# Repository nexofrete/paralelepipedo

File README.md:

# paralelepipedo

- [`tda7294/`](tda7294/README.md): amplificador de potência com TDA7294, com esquema, placa de face simples (PDF para transferência térmica e Gerber) e lista de material.

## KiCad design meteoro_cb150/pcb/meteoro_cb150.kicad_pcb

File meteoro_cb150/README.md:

# Meteoro Amplifier — Pré Power CB150

Montagem do esquema **Pré Power CB150** (Poi 20.60.40.012, rev. 0.0, 18/06/2007):
pré-amplificador com op-amps TL082/TL071, equalização passiva e amplificador
de potência classe AB discreto (±55 V, par 2SC5200/2SA1943).

Esta versão inclui **melhorias** sobre o esquema original (proteções, espelho
de corrente etc.); veja [Melhorias aplicadas](#melhorias-aplicadas). Os
componentes novos ou alterados estão marcados com ★ nas listas.

| Arquivo | Conteúdo |
|---|---|
| `esquema_eletrico.pdf` | **Esquema elétrico** da versão com melhorias (3 folhas: pré, potência, fonte); também em PNG (`esquema_*.png`) |
| `meteoro_cb150.cir` | Netlist SPICE completa (pré + potência), com modelos, pronta para o ngspice |
| `fonte.cir` | Fonte de alimentação (trafo, ponte KBPC606, filtros, reguladores ±12 V) |
| `pcb/meteoro_cb150_pcb.pdf` | **Placa de circuito impresso em PDF** (dupla face: as duas faces em 1:1 para transferência, montagem) |
| `pcb/meteoro_cb150_gerber.zip` | Gerber (RS-274X) + furação Excellon — para Proteus, fabricantes e qualquer CAM |
| `pcb/fabricacao/` | Os mesmos Gerbers soltos, DXF de cada face e posição dos componentes (CSV) |
| `pcb/relacao_componentes.csv` | Relação de componentes da placa (lista de compras), abre no Excel/LibreOffice |
| `pcb/meteoro_cb150.kicad_pcb` | A mesma placa em KiCad (abre no KiCad 7+, permite gerar Gerber) |

```sh
ngspice -b meteoro_cb150.cir   # ponto de operação, resposta AC e transiente 1 kHz
ngspice -b fonte.cir           # tensões da fonte
esquema/gerar.sh               # redesenha o esquema elétrico (precisa de schemdraw e matplotlib)
```

## Melhorias aplicadas

| Melhoria | Componentes | Para quê |
|---|---|---|
| Espelho de corrente no par diferencial | QM1, QM2 (MPSA42), RM1, RM2 (100 Ω) | menos distorção, offset ≈ 0 |
| Degeneração de emissor + cauda com 5,2 mA | R37, R38 (47 Ω), R15 3k3 → 1k6 | dobra o slew rate e mantém a estabilidade |
| Resistor de emissor e limitador no VAS | R19 560 Ω → 33 Ω no emissor de Q3, Q9 (BC546) | limita o VAS a ~18 mA (necessário para o limitador de saída funcionar) |
| Proteção contra curto na saída | QL1 (BC546), QL2 (BC556), R32/R34 (3k3), R33/R35 (1k) | limita a corrente de saída a ~8,5 A de pico |
| Resistor entre os drivers | R31 (220 Ω) entre emissores de Q5 e Q4 | desligamento mais rápido dos transistores de saída |
| Bobina de saída | L1: 1 µH (≈ 12 voltas de fio 1 mm) enrolada sobre resistor de 10 Ω/2 W | estabilidade com cabos longos e carga capacitiva |
| Offset equilibrado | R17 3k3 → 27k, R16 120 Ω → 1k | mesma impedância nas bases de Q1 e Q2 (ganho continua 28×) |
| Fusíveis nos trilhos | F1, F2 (5 A rápido, porta-fusível 5×20 de placa) | protege alto-falante e transistores se algo entrar em curto |
| Filtro maior | C19, C20 4700 µF → **10 000 µF**/63 V | menos ripple e queda de tensão em potência alta |

Não incluída na placa: **proteção contra DC no alto-falante com relé**. É
recomendada (módulo pronto de proteção para alto-falante, ligado entre SPEAKER
e a caixa).

## Resultado da simulação (carga 8 Ω, bias ≈ 35 mA)

Comparação do estágio de potência original com o melhorado (modelos de
transistor aproximados — valem como comparação):

| Grandeza | Original | Melhorado |
|---|---|---|
| Offset DC na saída | +120 mV | **+4 mV** |
| Distorção 1 kHz / 50 W | 0,21 % | **0,06 %** |
| Distorção 10 kHz / 50 W | 1,7 % | **0,24 %** |
| Distorção 20 kHz / 140 W | 11,6 % | **0,57 %** |
| Overshoot em degrau, 8 Ω ‖ 2,2 µF | 0,1 % | 0,4 % (estável) |
| Corrente de pico com saída em curto (0,1 Ω) | +21 A / −55 A (queima) | **±8,5 A** (limitada) |

| Grandeza | Valor |
|---|---|
| +12 V / −12 V (zener 1N4742A) | +12,1 V / −12,1 V |
| Trilhos com secundário 2 × 39 VAC | ±54 V |
| Referência da fonte de corrente (D3) | 9,1 V |
| Corrente de cauda do par Q1/Q2 | ≈ 5,2 mA |
| Corrente do VAS (Q3) | ≈ 10 mA |
| Ganho do power (R17/R16) | 1 + 27k/1k = 28× (29 dB) |

## Lista de materiais

### Resistores (1/4 W, 5% salvo indicação)
| Ref. | Valor | | Ref. | Valor |
|---|---|---|---|---|
| R1 | 1k5 | | R16 ★ | 1k |
| R2 | 220k | | R17 ★ | 27k |
| R3 | 2k7 | | R19 ★ | 33 Ω |
| R4 | 22k | | R20 | 2k2 **2 W** |
| R5 | 2k7 | | R21 | 1k5 |
| R6 | 12k | | R22 | 680 Ω |
| R7 | 270k | | R23, R24 | 2k7 (½ W) |
| R8 | 22k | | R26 | 4,7 Ω **2 W** |
| R9 | 2k2 | | R27, R28 | 0,33 Ω **5 W** |
| R10 | 47k | | R29 | 12k |
| R12 | 4k7 | | R30 | 470 Ω |
| R13 | 10k | | R50 | 47k |
| R14 | 4k7 | | R88 | 2k2 **2 W** |
| R15 ★ | 1k6 | | R100 | 5k6 (½ W) |
| R101 | 1k | | R102 | 27k |
| R31 ★ | 220 Ω | | R32, R34 ★ | 3k3 |
| R33, R35 ★ | 1k | | R37, R38 ★ | 47 Ω |
| RM1, RM2 ★ | 100 Ω | | L1 ★ | 10 Ω **2 W** com 1 µH enrolado (ver melhorias) |

### Potenciômetros
| Ref. | Valor | Função |
|---|---|---|
| RV1 | 20k linear (B) | ganho/master do CI2 (ligado como reostato) |
| RV2 | 100k linear (B) | agudos |
| RV3 | 10k linear (B) | equalização (reostato, cursor ligado a um extremo) |
| RV4 | 50k log (A) | equalização (reostato) |
| RV5 | 1k trimpot multivoltas | **ajuste de corrente de repouso (bias)** |

### Capacitores
| Ref. | Valor | Tipo |
|---|---|---|
| C1 | 22 nF | poliéster |
| C2 | 10 µF/63 V | eletrolítico |
| C3, C13 | 330 pF | cerâmico |
| C4, C10 | 2,2 nF | poliéster |
| C5 | 100 nF | poliéster |
| C6 | 47 nF | poliéster |
| C7 | 120 pF | cerâmico |
| C8 | 22 µF/63 V | eletrolítico |
| C9 | 1 µF | poliéster |
| C11 | 22 nF | poliéster |
| C12 | 220 µF/63 V | eletrolítico |
| C14 | 470 pF | cerâmico 100 V |
| C15 | 47 µF/63 V | eletrolítico (no esquema 50 V; use 63 V) |
| C16 | 10 µF/63 V | eletrolítico |
| C17 | 100 nF/250 V | poliéster |
| C18 | 10 µF/63 V | eletrolítico |
| C19, C20 ★ | 10 000 µF/63 V | eletrolítico snap-in (35 mm) |
| C21 | 1 µF | poliéster |
| C100 | 2,2 µF/63 V | eletrolítico |
| C101 | 4,7 µF/50 V | eletrolítico |

> No esquema "22K", "47K", "100K", "2K2" em capacitores significam **nF**
> (22K = 22 nF, 100K = 100 nF, 2K2 = 2,2 nF).

### Semicondutores
| Ref. | Peça | Observação |
|---|---|---|
| CI1 | TL082 | duplo (CI1A + CI1B) |
| CI2 | TL071 | pinos 1/5 (BAL) sem ligação |
| Q1, Q2 | MPSA92 (PNP 300 V) | parear hFE |
| Q3, Q5 | BD139 | Q5 em dissipador pequeno |
| Q4 | BD140 | em dissipador pequeno |
| Q6 | 2SA1943 | dissipador principal, isolado (mica/silicone) |
| Q7 | 2SC5200 | dissipador principal, isolado |
| Q8 | MPSA42 | **colar no dissipador** dos transistores de saída (compensação térmica) |
| QM1, QM2 ★ | MPSA42 | espelho de corrente (de preferência com hFE parecido) |
| Q9, QL1 ★ | BC546 | limitadores (VAS e saída positiva) |
| QL2 ★ | BC556 | limitador (saída negativa) |
| D1, D2 | 1N4742A | zener 12 V 1 W |
| D3 | 1N4739 | zener 9,1 V (a nota do esquema cita "D100 – 1N4742", ver observações) |
| PT1 | KBPC606 | ponte retificadora 6 A, no chassi |

### Outros
- TR: transformador 127/220 V → **2 × 39 VAC** com center tap, ≥ 250 VA, fusível no primário.
- J1: jaque P10 mono; CH1: chave 1 polo (ganho); bornes SPEAKER e LINE OUT.
- Dissipador ≥ 0,5 °C/W para Q6/Q7, isoladores, pasta térmica.
- ★ F1, F2: fusíveis 5×20 mm de 5 A rápidos + porta-fusíveis de placa.

## Placa de circuito impresso (`pcb/`)

Placa **dupla face** de 230 × 145 mm, **sem jumpers** (só 4 vias), com 98
itens: os componentes do esquema com as melhorias, conectores para as peças
de painel, 2 capacitores de desacoplamento de 100 nF nos op-amps (CD1/CD2) e
a ponte de terra JGND. As melhorias acrescentam ligações que cruzam o estágio
de saída; em face simples isso exigiria cerca de 30 jumpers, por isso a placa
passou a ser dupla face.

- **Relação de componentes** (páginas 2–4 do PDF e `relacao_componentes.csv`):
  tirada da própria placa, agrupada por valor, com as peças de painel à parte.
- **Cobre do lado da solda** (B.Cu), em escala 1:1.
- **Cobre do lado dos componentes** (F.Cu), já espelhado para a
  transferência. Alinhe as duas faces pelos 4 furos de fixação.
- **Montagem**: lado dos componentes (referência e valor de cada peça).
- **Sobreposição**: as duas faces juntas.
- Imprima a 100% (sem "ajustar à página"); o contorno deve medir exatamente
  230 × 145 mm.
- Em placa caseira (sem furos metalizados): passe um fio nas 4 vias e solde
  dos dois lados, e solde **também por cima** os pads que têm trilha na face
  de cima. Ou mande fabricar: o `.kicad_pcb` gera Gerber no KiCad 7+.
- O GND de sinal tem plano de cobre nas duas faces. O GND de potência
  (capacitores de filtro, Zobel, alto-falante) só se une a ele pela ponte
  **JGND** — aterramento em estrela.
- Q4/Q5/Q6/Q7 ficam na borda superior para um único dissipador; Q8 deve ficar
  encostado nele (com fios, se preciso) para o bias acompanhar a temperatura.
- Trilhas: 0,75 mm (sinal), 1,2 mm (GND, bases), 2,0 mm (±55 V, saída,
  emissores); isolação mínima de 0,5 mm, verificada com o DRC do KiCad
  (`verificar.py`).

### Abrir no Proteus

O formato de projeto do Proteus (`.pdsprj`) é fechado, então não há como
gerá-lo diretamente. Use os arquivos de fabricação:

- **Gerber**: no Proteus 8, *File → Import → Gerber* (ou o *Gerber Viewer*),
  apontando para os arquivos de `meteoro_cb150_gerber.zip`
  (`.gtl` = cobre de cima, `.gbl` = cobre de baixo, `.gto` = serigrafia,
  `.gts/.gbs` = máscara, `.gm1` = contorno, `.drl` = furos). Serve para ver,
  conferir e gerar a placa, mas vem como desenho, sem netlist editável.
- **DXF** (`fabricacao/dxf/`): cada face como desenho, para importar como
  gráfico.
- Para **simular** no Proteus, o esquema precisa ser desenhado no ISIS; use
  `meteoro_cb150.cir` e a lista de componentes como referência das ligações.

Os mesmos Gerbers servem para mandar fabricar (JLCPCB, PCBWay etc.): placa
de 2 camadas, 230 × 145 mm, 1,6 mm, cobre 1 oz (2 oz se possível, pelas
correntes da saída).

Para regenerar (precisa de KiCad 7, numpy, scipy, Pillow, reportlab):

```sh
cd pcb
LAYERS=2 POUR=GND python3 gerar_pcb.py 62   # posição em posicao_62.json + roteamento (~5 min)
python3 verificar.py                          # DRC
python3 lista.py                              # relacao_componentes.csv
python3 gerar_pdf.py                          # meteoro_cb150_pcb.pdf
mkdir -p fabricacao/gerber && kicad-cli pcb export gerbers --no-x2 \
  -l F.Cu,B.Cu,F.Mask,B.Mask,F.SilkS,Edge.Cuts -o fabricacao/gerber/ meteoro_cb150.kicad_pcb
kicad-cli pcb export drill -o fabricacao/gerber/ meteoro_cb150.kicad_pcb
```

## Como ligar (por blocos)

1. **Entrada / CI1A** — J1 → R1 → C1 → pino 3. R2 do pino 3 ao terra.
   Realimentação: R4 ‖ C3 entre pinos 1 e 2, e R50 + C11 em série também do
   pino 1 ao pino 2. Do pino 2: C2 (+ no pino 2) → R3 → R13 → terra.
   **CH1** curto-circuita R13 (fechada = mais ganho: 9× em vez de 2,7×).
2. **Equalização** — saída do CI1A → C4 → extremo direito de RV2; → R6 → extremo
   esquerdo de RV2. Esse mesmo ponto (R6/RV2) vai a C5 e a RV4 (reostato);
   do outro lado, C5/RV4 → R5 ‖ RV3 (reostato) → terra. Cursor de RV2 → C6 →
   pino 5 do CI1B, com R7 270k ao terra.
3. **CI1B** — R8 ‖ C7 entre pinos 7 e 6; pino 6 → C8 (+ no pino 6) → R9 → terra.
   Saída → R10 47k e → R12 4k7 + C10 2n2 em série, ambos ao mesmo nó → C9.
4. **CI2 (TL071)** — inversor: C9 → pino 2; pino 3 no terra; RV1 (reostato) ‖ C13
   entre pinos 6 e 2. Alimentação dos três op-amps: +12 V (pino 8 do TL082 /
   pino 7 do TL071) e −12 V (pino 4). Ponha 100 nF de desacoplamento junto de
   cada CI.
5. **Entrada do power** — pino 6 do CI2 → R14 → C100 (+ do lado de R14) → base de
   Q1; R102 da base de Q1 ao terra; R101 + C101 em série da base de Q1 ao nó de
   realimentação (base de Q2).
6. **Par diferencial** — +55 V → R100 → catodo de D3 (anodo no terra), C16 em
   paralelo; desse nó (≈ 9,1 V) → R15 (1k6) → R37/R38 (47 Ω) → emissores de Q1 e Q2.
   Espelho: coletor de Q2 → coletor e base de QM2 e base de QM1; coletor de
   QM1 = coletor de Q1 = base de Q3. Emissores de QM1/QM2 → RM1/RM2 (100 Ω) → −55 V.
7. **Realimentação** — saída → R17 → base de Q2; base de Q2 → R16 → C12 (+ do
   lado de R16) → terra.
8. **VAS** — emissor de Q3 → R19 (33 Ω) → −55 V; C14 entre coletor e base de Q3.
   Q9 (BC546): base no emissor de Q3, coletor na base de Q3, emissor no −55 V.
9. **Bias (Q8)** — coletor de Q8 → R21 → RV5 → R22 → emissor; cursor de RV5 → base
   de Q8. Emissor de Q8 = coletor de Q3 = base de Q4. Coletor de Q8 = base de Q5.
10. **Bootstrap** — base de Q5 → R23 → nó → R24 → +55 V; C15 do nó à saída
    (+ do lado do nó).
11. **Saída** — Q5→Q7 (NPN) e Q4→Q6 (PNP) em Darlington; emissores de Q7/Q6 por
    R28/R27 (0,33 Ω/5 W) à saída. R31 (220 Ω) entre os emissores de Q5 e Q4.
    Limitadores: QL1 (C na base de Q5, E na saída, B no divisor R32/R33 entre
    emissor de Q7 e saída); QL2 igual no lado negativo (C na base de Q4, divisor R34/R35).
    Zobel R26 + C17 da saída ao terra. Saída → L1 (1 µH ‖ 10 Ω) → borne SPEAKER.
    LINE OUT: saída → R29 → nó (R30 ao terra) → C21 → borne.
12. **Fonte** — secundário → KBPC606 → C20 (+55 V) e C19 (−55 V), center tap no
    terra. Dos capacitores para o amplificador, passando pelos fusíveis F1/F2. ±12 V: R88/R20 (2k2 2 W) + zener D1/D2, C18 no −12 V.
    Use **terra em estrela**: terra de sinal (J1, R2, R9, C12) separado do terra
    de potência (C19/C20, Zobel, alto-falante), unidos num só ponto nos capacitores.

## Primeira ligação e calibração

1. Antes de ligar: confira polaridade de todos os eletrolíticos e zeners, e
   isolação dos transistores de saída ao dissipador (multímetro em continuidade).
2. Gire **RV5** para a **mínima** corrente (menor resistência entre cursor e R21).
3. Ligue pela primeira vez **sem alto-falante** e com **lâmpada em série** no
   primário (60–100 W) ou com fonte variável.
4. Meça: ±55 V, ±12 V, ≈ 9,1 V em D3, saída **< ±50 mV** DC.
5. Ajuste **RV5** medindo a tensão sobre R27 ou R28: **7–10 mV**
   (≈ 20–30 mA de repouso). Deixe aquecer 15 min e reajuste.
   Com as melhorias, o RV5 no meio do curso dá pouca corrente — é normal ter
   de girar mais.
6. Teste do limitador (opcional): com o alto-falante desligado e volume baixo,
   encoste uma carga de 4 Ω; a corrente não deve passar de ~8 A de pico.
7. Só então ligue o alto-falante (8 Ω; 4 Ω no máximo, com bom dissipador).

## Observações sobre o esquema

- A nota do esquema lista R100, R101, R102, C100, C101 e "D100 – 1N4742" como
  componentes acrescentados em manutenção/revisão. O desenho mostra D3 = 1N4739
  (9,1 V), o que dá a polarização correta da cauda; com 1N4742 (12 V) a corrente
  do par sobe para ≈ 3,4 mA — também funciona.
- R101 + C101 ligam a base de Q1 à base de Q2 como desenhado; isso atenua o sinal
  vindo do CI2 (divisor R14 × R101). Na simulação eles ajudam na estabilidade
  com carga capacitiva, então foram mantidos.
- Com ±55 V e um único par de saída, use carga de 8 Ω para uso contínuo
  (≈ 150 W); em 4 Ω os 2SC5200/2SA1943 trabalham no limite da SOA (o limitador
  de corrente protege contra curto, mas não substitui um segundo par de saída).
- Os modelos dos transistores e op-amps na netlist são aproximados — servem para
  verificar ligações e polarização, não para prever distorção com precisão.

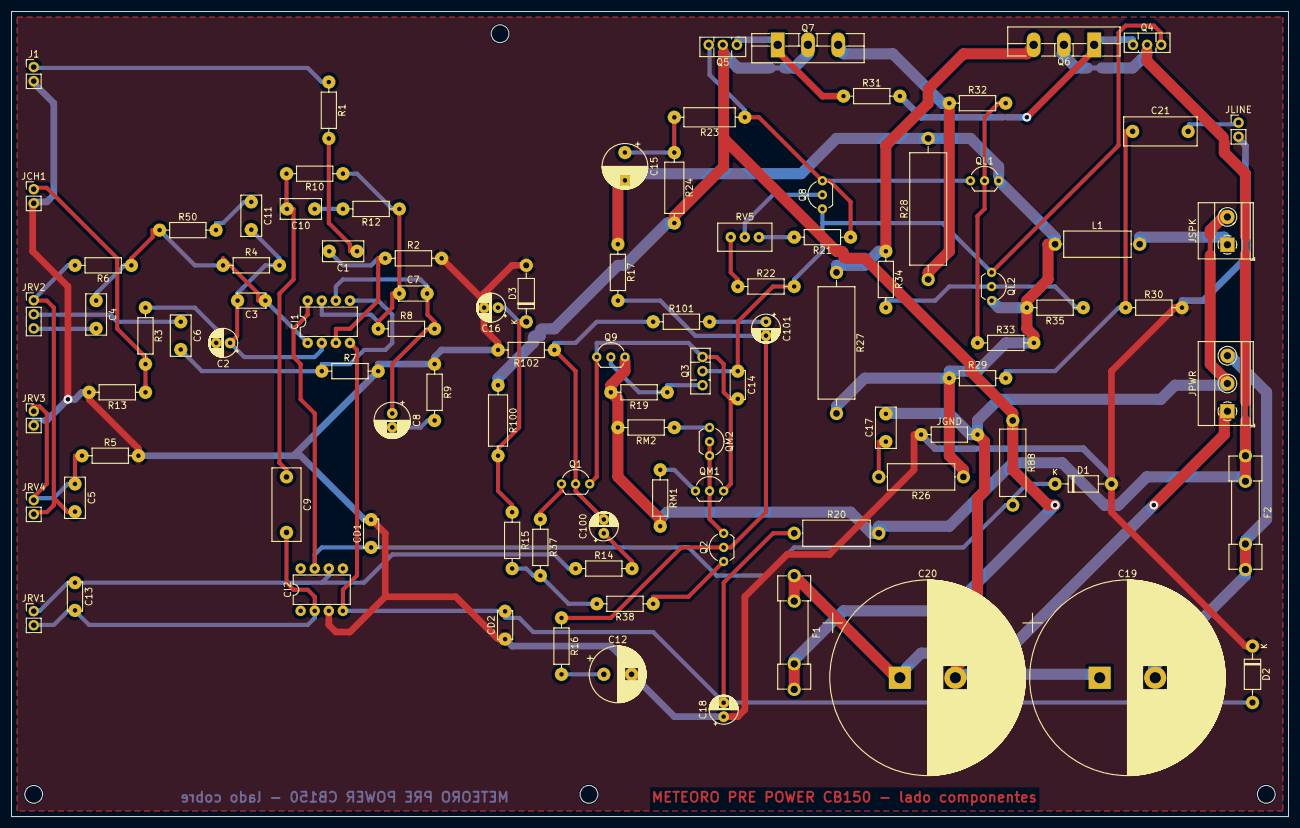
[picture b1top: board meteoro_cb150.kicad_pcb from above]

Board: 2 copper layers, 230.0 x 145.0 mm, 98 parts (0 on the bottom side), 59 nets.

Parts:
C1, C11: 22n; C_Rect_L7.2mm_W3.5mm_P5.00mm_FKS2_FKP2_MKS2_MKP2
C2, C16, C18: 10u/63V; CP_Radial_D5.0mm_P2.50mm
C3, C13: 330p; C_Disc_D5.0mm_W2.5mm_P5.00mm
C4, C10: 2n2; C_Rect_L7.2mm_W3.5mm_P5.00mm_FKS2_FKP2_MKS2_MKP2
C5, C17: 100n; C_Rect_L7.2mm_W3.5mm_P5.00mm_FKS2_FKP2_MKS2_MKP2
C6: 47n; C_Rect_L7.2mm_W3.5mm_P5.00mm_FKS2_FKP2_MKS2_MKP2
C7: 120p; C_Disc_D5.0mm_W2.5mm_P5.00mm
C8: 22u/63V; CP_Radial_D6.3mm_P2.50mm
C9, C21: 1u; C_Rect_L13.0mm_W5.0mm_P10.00mm_FKS3_FKP3_MKS4
C12: 220u/63V; CP_Radial_D10.0mm_P5.00mm
C14: 470p; C_Disc_D5.0mm_W2.5mm_P5.00mm
C15: 47u/63V; CP_Radial_D8.0mm_P5.00mm
C19, C20: 10000u/63V; CP_Radial_D35.0mm_P10.00mm_SnapIn
C100: 2u2/63V; CP_Radial_D5.0mm_P2.50mm
C101: 4u7/50V; CP_Radial_D5.0mm_P2.50mm
CD1, CD2: 100n; C_Disc_D5.0mm_W2.5mm_P5.00mm
CI1: TL082; DIP-8_W7.62mm
CI2: TL071; DIP-8_W7.62mm
D1, D2: 1N4742A; D_DO-41_SOD81_P10.16mm_Horizontal
D3: 1N4739; D_DO-41_SOD81_P10.16mm_Horizontal
F1, F2: 5A rapido; Fuseholder_Clip-5x20mm_Littelfuse_100_Inline_P20.50x4.60mm_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
J1: ENTRADA; PinHeader_1x02_P2.54mm_Vertical
JCH1: CH1; PinHeader_1x02_P2.54mm_Vertical
JGND: PONTE FIO; R_Axial_DIN0207_L6.3mm_D2.5mm_P10.16mm_Horizontal
JLINE: LINE OUT; PinHeader_1x02_P2.54mm_Vertical
JPWR: +55 GND -55; TerminalBlock_Phoenix_MKDS-1,5-3_1x03_P5.00mm_Horizontal
JRV1: RV1 20KB; PinHeader_1x02_P2.54mm_Vertical
JRV2: RV2 100KB; PinHeader_1x03_P2.54mm_Vertical
JRV3: RV3 10KB; PinHeader_1x02_P2.54mm_Vertical
JRV4: RV4 50KA; PinHeader_1x02_P2.54mm_Vertical
JSPK: SPEAKER; TerminalBlock_Phoenix_MKDS-1,5-2_1x02_P5.00mm_Horizontal
L1: 10R 2W + 1uH; R_Axial_DIN0414_L11.9mm_D4.5mm_P15.24mm_Horizontal
Q1, Q2: MPSA92; TO-92_Inline_Wide
Q3, Q5: BD139; TO-126-3_Vertical
Q4: BD140; TO-126-3_Vertical
Q6: 2SA1943; TO-264-3_Vertical
Q7: 2SC5200; TO-264-3_Vertical
Q8: MPSA42; TO-92_Inline_Wide
Q9: BC546; TO-92_Inline_Wide
QL1: BC546; TO-92_Inline_Wide
QL2: BC556; TO-92_Inline_Wide
QM1, QM2: MPSA42; TO-92_Inline_Wide
R1, R21: 1k5; R_Axial_DIN0207_L6.3mm_D2.5mm_P10.16mm_Horizontal
R2: 220k; R_Axial_DIN0207_L6.3mm_D2.5mm_P10.16mm_Horizontal
R3, R5: 2k7; R_Axial_DIN0207_L6.3mm_D2.5mm_P10.16mm_Horizontal
R4, R8: 22k; R_Axial_DIN0207_L6.3mm_D2.5mm_P10.16mm_Horizontal
R6, R29: 12k; R_Axial_DIN0207_L6.3mm_D2.5mm_P10.16mm_Horizontal
R7: 270k; R_Axial_DIN0207_L6.3mm_D2.5mm_P10.16mm_Horizontal
R9: 2k2; R_Axial_DIN0207_L6.3mm_D2.5mm_P10.16mm_Horizontal
R10, R50: 47k; R_Axial_DIN0207_L6.3mm_D2.5mm_P10.16mm_Horizontal
R12, R14: 4k7; R_Axial_DIN0207_L6.3mm_D2.5mm_P10.16mm_Horizontal
R13: 10k; R_Axial_DIN0207_L6.3mm_D2.5mm_P10.16mm_Horizontal
R15: 1k6; R_Axial_DIN0207_L6.3mm_D2.5mm_P10.16mm_Horizontal
R16, R33, R35, R101: 1k; R_Axial_DIN0207_L6.3mm_D2.5mm_P10.16mm_Horizontal
R17, R102: 27k; R_Axial_DIN0207_L6.3mm_D2.5mm_P10.16mm_Horizontal
R19: 33R; R_Axial_DIN0207_L6.3mm_D2.5mm_P10.16mm_Horizontal
R20, R88: 2k2 2W; R_Axial_DIN0414_L11.9mm_D4.5mm_P15.24mm_Horizontal
R22: 680R; R_Axial_DIN0207_L6.3mm_D2.5mm_P10.16mm_Horizontal
R23, R24: 2k7; R_Axial_DIN0309_L9.0mm_D3.2mm_P12.70mm_Horizontal
R26: 4R7 2W; R_Axial_DIN0414_L11.9mm_D4.5mm_P15.24mm_Horizontal
R27, R28: 0R33 5W; R_Axial_Power_L20.0mm_W6.4mm_P25.40mm
R30: 470R; R_Axial_DIN0207_L6.3mm_D2.5mm_P10.16mm_Horizontal
R31: 220R; R_Axial_DIN0207_L6.3mm_D2.5mm_P10.16mm_Horizontal
R32, R34: 3k3; R_Axial_DIN0207_L6.3mm_D2.5mm_P10.16mm_Horizontal
R37, R38: 47R; R_Axial_DIN0207_L6.3mm_D2.5mm_P10.16mm_Horizontal
R100: 5k6; R_Axial_DIN0309_L9.0mm_D3.2mm_P12.70mm_Horizontal
RM1, RM2: 100R; R_Axial_DIN0207_L6.3mm_D2.5mm_P10.16mm_Horizontal
RV5: 1k; Potentiometer_Bourns_3296W_Vertical

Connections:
BIAST: Q5.3, Q8.3, QL1.1, R21.1, R23.1
E1: Q1.1, R37.1
E2: Q2.1, R38.1
E3: Q3.1, Q9.2, R19.1
EDIF: R15.2, R37.2, R38.2
EM1: QM1.1, RM1.1
EM2: QM2.1, RM2.1
FB: C101.2, Q2.2, R16.1, R17.2
GND: C12.2, C16.2, C18.1, CD1.2, CD2.1, CI2.3, D1.2, D2.1, D3.2, J1.2, JCH1.2, JGND.1, JLINE.2, JRV3.2, R2.2, R5.2, R7.2, R9.1, R13.2, R30.2, R102.2
GNDP: C17.2, C19.1, C20.2, JGND.2, JPWR.2, JSPK.2
IN: J1.1, R1.1
IN1BN: C7.2, C8.1, CI1.6, R8.2
IN1BP: C6.2, CI1.5, R7.1
IN1N: C2.1, C3.2, C11.2, CI1.2, R4.2
IN1P: C1.2, CI1.3, R2.1
IN2N: C9.2, C13.2, CI2.2, JRV1.2
LINE: C21.1, R29.2, R30.1
LINEOUT: C21.2, JLINE.1
N1: C1.1, R1.2
N2: C2.2, R3.1
N3: JCH1.1, R3.2, R13.1
N9: C8.2, R9.2
N10: C9.1, C10.2, R10.2
N12: C10.1, R12.2
N14: C100.1, R14.2
N16: C12.1, R16.2
N26: C17.1, R26.2
N50: C11.1, R50.2
N101: C101.1, R101.2
NBOOT: C15.1, R23.2, R24.1
NM: Q2.3, QM1.2, QM2.2, QM2.3
OUT: C15.2, L1.1, QL1.3, QL2.3, R17.1, R26.1, R27.2, R28.2, R29.1, R33.2, R35.2
OUT1: C3.1, C4.1, CI1.1, R4.1, R6.1, R50.1
OUT2: C7.1, CI1.7, R8.1, R10.1, R12.1
OUT3: C13.1, CI2.6, JRV1.1, R14.1
Q6B: Q4.1, Q6.1, R31.2
Q6E: Q6.3, R27.1, R34.1
Q7B: Q5.1, Q7.1, R31.1
Q7E: Q7.3, R28.1, R32.1
Q8B: Q8.2, RV5.2
QB1: C100.2, Q1.2, R101.1, R102.1
QL1B: QL1.2, R32.2, R33.1
QL2B: QL2.2, R34.2, R35.1
RV2W: C6.1, JRV2.2
RV5B: R22.1, RV5.3
RV5T: R21.2, RV5.1
SPK: JSPK.1, L1.2
TONEM: C5.2, JRV2.1, JRV4.2, R6.2
TONEN: C5.1, JRV3.1, JRV4.1, R5.1
TREB: C4.2, JRV2.3
VAS: C14.1, Q3.2, Q4.3, Q8.1, QL2.1, R22.2
VASB: C14.2, Q1.3, Q3.3, Q9.1, QM1.3
VN12: C18.2, CD2.2, CI1.4, CI2.4, D2.2, R20.1
VN55: F2.1, Q4.2, Q6.2, Q9.3, R19.2, R20.2, RM1.2, RM2.2
VN55R: C19.2, F2.2, JPWR.3
VP12: CD1.1, CI1.8, CI2.7, D1.1, R88.2
VP55: F1.2, Q5.2, Q7.2, R24.2, R88.1, R100.1
VP55R: C20.1, F1.1, JPWR.1
VZ: C16.1, D3.1, R15.1, R100.2

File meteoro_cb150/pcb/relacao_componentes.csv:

Qtd;Valor;Descricao;Referencias;Local
2;2k7;Resistor 1/2 W;R23, R24;placa
1;5k6;Resistor 1/2 W;R100;placa
2;1k5;Resistor 1/4 W;R1, R21;placa
1;220k;Resistor 1/4 W;R2;placa
2;2k7;Resistor 1/4 W;R3, R5;placa
2;22k;Resistor 1/4 W;R4, R8;placa
2;12k;Resistor 1/4 W;R6, R29;placa
1;270k;Resistor 1/4 W;R7;placa
1;2k2;Resistor 1/4 W;R9;placa
2;47k;Resistor 1/4 W;R10, R50;placa
2;4k7;Resistor 1/4 W;R12, R14;placa
1;10k;Resistor 1/4 W;R13;placa
1;1k6;Resistor 1/4 W;R15;placa
4;1k;Resistor 1/4 W;R16, R33, R35, R101;placa
2;27k;Resistor 1/4 W;R17, R102;placa
1;33R;Resistor 1/4 W;R19;placa
1;680R;Resistor 1/4 W;R22;placa
1;470R;Resistor 1/4 W;R30;placa
1;220R;Resistor 1/4 W;R31;placa
2;3k3;Resistor 1/4 W;R32, R34;placa
2;47R;Resistor 1/4 W;R37, R38;placa
2;100R;Resistor 1/4 W;RM1, RM2;placa
1;10R 2W + 1uH;Resistor 10 R 2 W + bobina 1 uH (12 voltas, fio 1 mm);L1;placa
2;2k2 2W;Resistor 2 W;R20, R88;placa
1;4R7 2W;Resistor 2 W;R26;placa
2;0R33 5W;Resistor 5 W (fio);R27, R28;placa
2;330p;Capacitor ceramico 100 V;C3, C13;placa
1;120p;Capacitor ceramico 100 V;C7;placa
1;470p;Capacitor ceramico 100 V;C14;placa
2;100n;Capacitor ceramico 100 V;CD1, CD2;placa
2;22n;Capacitor de poliester 100 V;C1, C11;placa
2;2n2;Capacitor de poliester 100 V;C4, C10;placa
2;100n;Capacitor de poliester 100 V;C5, C17;placa
1;47n;Capacitor de poliester 100 V;C6;placa
2;1u;Capacitor de poliester 100 V;C9, C21;placa
3;10u/63V;Capacitor eletrolitico;C2, C16, C18;placa
1;22u/63V;Capacitor eletrolitico;C8;placa
1;220u/63V;Capacitor eletrolitico;C12;placa
1;47u/63V;Capacitor eletrolitico;C15;placa
1;2u2/63V;Capacitor eletrolitico;C100;placa
1;4u7/50V;Capacitor eletrolitico;C101;placa
2;10000u/63V;Capacitor eletrolitico snap-in 35 mm;C19, C20;placa
2;1N4742A;Diodo zener 1 W;D1, D2;placa
1;1N4739;Diodo zener 1 W;D3;placa
2;BD139;Transistor TO-126;Q3, Q5;placa
1;BD140;Transistor TO-126;Q4;placa
1;2SA1943;Transistor TO-264 (no dissipador);Q6;placa
1;2SC5200;Transistor TO-264 (no dissipador);Q7;placa
2;MPSA92;Transistor TO-92;Q1, Q2;placa
3;MPSA42;Transistor TO-92;Q8, QM1, QM2;placa
2;BC546;Transistor TO-92;Q9, QL1;placa
1;BC556;Transistor TO-92;QL2;placa
1;TL082;Circuito integrado DIP-8;CI1;placa
1;TL071;Circuito integrado DIP-8;CI2;placa
1;1k;Trimpot multivoltas 3296W;RV5;placa
2;5A rapido;Porta-fusivel de placa 5x20 mm;F1, F2;placa
1;+55 GND -55;Borne parafuso 5 mm;JPWR;placa
1;SPEAKER;Borne parafuso 5 mm;JSPK;placa
1;ENTRADA;Conector / pontos para fio do painel;J1;placa
1;CH1;Conector / pontos para fio do painel;JCH1;placa
1;LINE OUT;Conector / pontos para fio do painel;JLINE;placa
1;RV1 20KB;Conector / pontos para fio do painel;JRV1;placa
1;RV2 100KB;Conector / pontos para fio do painel;JRV2;placa
1;RV3 10KB;Conector / pontos para fio do painel;JRV3;placa
1;RV4 50KA;Conector / pontos para fio do painel;JRV4;placa
1;PONTE FIO;Ponte de fio (terra em estrela);JGND;placa
1;20k linear (B);Potenciometro (ganho/master) - liga em JRV1;RV1;fora da placa
1;100k linear (B);Potenciometro (agudos) - liga em JRV2;RV2;fora da placa
1;10k linear (B);Potenciometro (equalizacao) - liga em JRV3;RV3;fora da placa
1;50k log (A);Potenciometro (equalizacao) - liga em JRV4;RV4;fora da placa
1;P10 mono;Jaque de entrada - liga em J1;J1 (painel);fora da placa
1;1 polo;Chave de ganho - liga em JCH1;CH1;fora da placa
1;KBPC606;Ponte retificadora 6 A (no chassi) - liga em JPWR;PT1;fora da placa
1;2 x 39 VAC, >= 250 VA;Transformador com center tap + fusivel no primario;TR;fora da placa
1;>= 0,5 C/W;Dissipador para Q4, Q5, Q6, Q7 (+ isoladores e pasta termica);-;fora da placa
2;5 A rapido;Fusivel 5x20 mm (vai nos porta-fusiveis F1/F2);F1, F2;fora da placa
2;DIP-8;Soquete para CI1 e CI2;CI1, CI2;fora da placa
